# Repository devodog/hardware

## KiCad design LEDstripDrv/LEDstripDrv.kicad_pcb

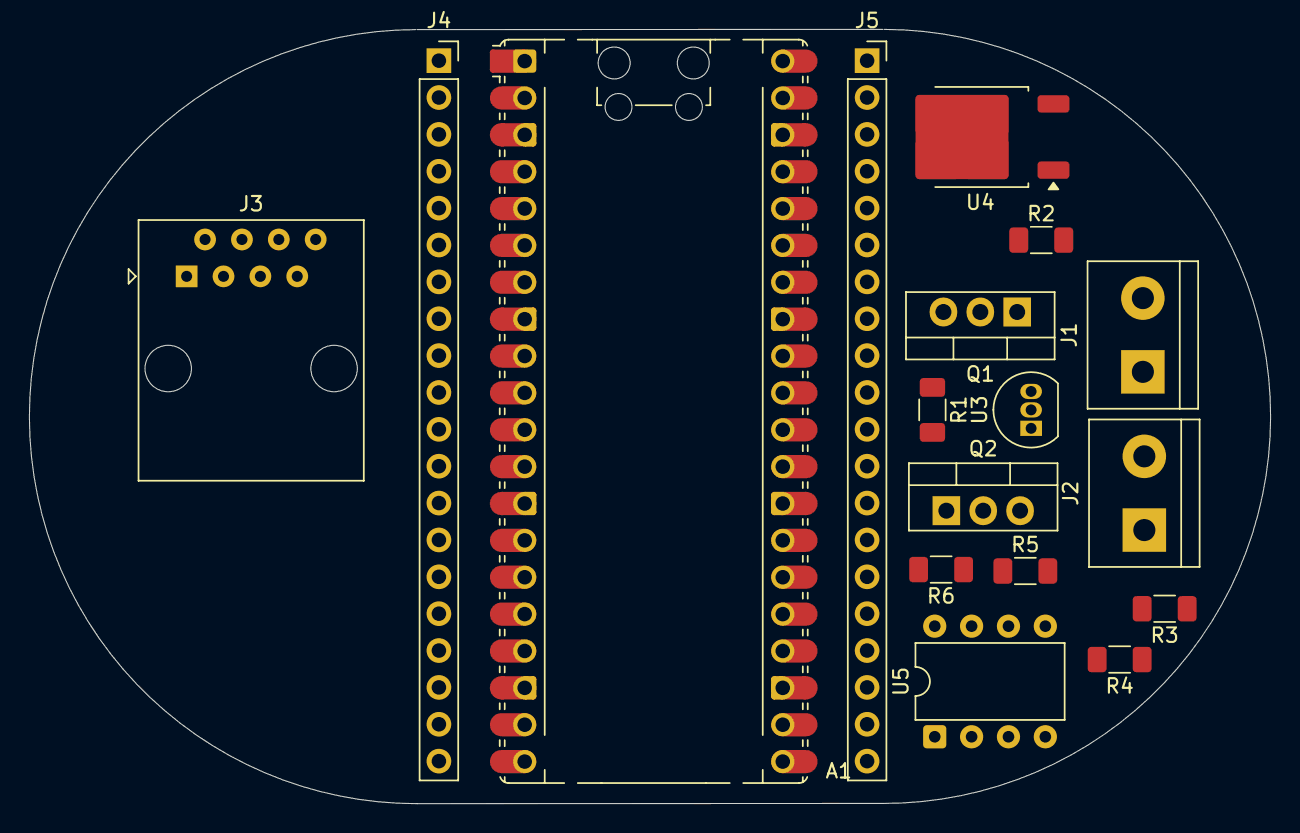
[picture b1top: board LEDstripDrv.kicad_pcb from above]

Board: 2 copper layers, 85.5 x 53.3 mm, 17 parts (0 on the bottom side), 43 nets, no tracks yet.

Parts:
A1: RaspberryPi_Pico; RaspberryPi_Pico_Common_Unspecified
J1, J2: Screw_Terminal_01x02; TerminalBlock_bornier-2_P5.08mm
J3: RJ45; RJ45_Amphenol_54602-x08_Horizontal
J4, J5: Conn_01x20_Pin; PinSocket_1x20_P2.54mm_Vertical
Q1, Q2: IRF540N; TO-220-3_Vertical
R1, R5: 100; R_1206_3216Metric_Pad1.30x1.75mm_HandSolder
R2, R3, R4, R6: 1k; R_1206_3216Metric_Pad1.30x1.75mm_HandSolder
U3: LM35-LP; TO-92_Inline
U4: LF50_TO252; TO-252-2
U5: PC827; DIP-8_W7.62mm

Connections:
+24V: J1.1, J2.1, J3.7, J3.8, U4.1 (VI), U5.6, U5.8
GND: A1.33 (AGND), J3.1, J3.2, Q1.3 (S), Q2.3 (S), R2.1, R3.1, R4.1, R6.1, U3.3 (GND), U4.2 (GND)
unnamed: A1.36 (3V3), J3.6, J5.5
unnamed: A1.37 (3V3_EN), J5.4
unnamed: A1.35 (ADC_VREF), J5.6
unnamed: A1.1 (GPIO0), J4.1
unnamed: A1.2 (GPIO1), J4.2
unnamed: A1.4 (GPIO2), J4.4
unnamed: A1.5 (GPIO3), J4.5
unnamed: A1.6 (GPIO4), J4.6
unnamed: A1.7 (GPIO5), J4.7
unnamed: A1.9 (GPIO6), J4.9
unnamed: A1.10 (GPIO7), J4.10
unnamed: A1.11 (GPIO8), J4.11
unnamed: A1.12 (GPIO9), J4.12
unnamed: A1.14 (GPIO10), J4.14
unnamed: A1.15 (GPIO11), J4.15
unnamed: A1.16 (GPIO12), J4.16
unnamed: A1.17 (GPIO13), J4.17
unnamed: A1.19 (GPIO14), J4.19
unnamed: A1.20 (GPIO15), J4.20
unnamed: A1.21 (GPIO16), J5.20, U5.1
unnamed: A1.22 (GPIO17), J5.19, U5.3
unnamed: A1.24 (GPIO18), J5.17
unnamed: A1.25 (GPIO19), J5.16
unnamed: A1.26 (GPIO20), J5.15
unnamed: A1.27 (GPIO21), J5.14
unnamed: A1.29 (GPIO22), J5.12
unnamed: A1.31 (GPIO26_ADC0), J3.3, J5.10
unnamed: A1.32 (GPIO27_ADC1), J3.4, J5.9
unnamed: A1.34 (GPIO28_ADC2), J5.7, U3.2 (V_{OUT})
unnamed: A1.30 (RUN), J3.5, J5.11
unnamed: A1.40 (VBUS), J5.1
unnamed: A1.39 (VSYS), J5.2, U3.1 (+V_{S}), U4.3 (VO)
unnamed: J1.2, Q1.2 (D)
unnamed: J2.2, Q2.2 (D)
unnamed: A1.3 (GND), A1.8 (GND), A1.13 (GND), A1.18 (GND), A1.23 (GND), A1.28 (GND), A1.38 (GND), J4.3, J4.8, J4.13, J4.18, J5.3, J5.8, J5.13, J5.18
unnamed: Q1.1 (G), R1.2, R2.2
unnamed: Q2.1 (G), R5.2, R6.2
unnamed: R1.1, U5.7
unnamed: R3.2, U5.2
unnamed: R4.2, U5.4
unnamed: R5.1, U5.5

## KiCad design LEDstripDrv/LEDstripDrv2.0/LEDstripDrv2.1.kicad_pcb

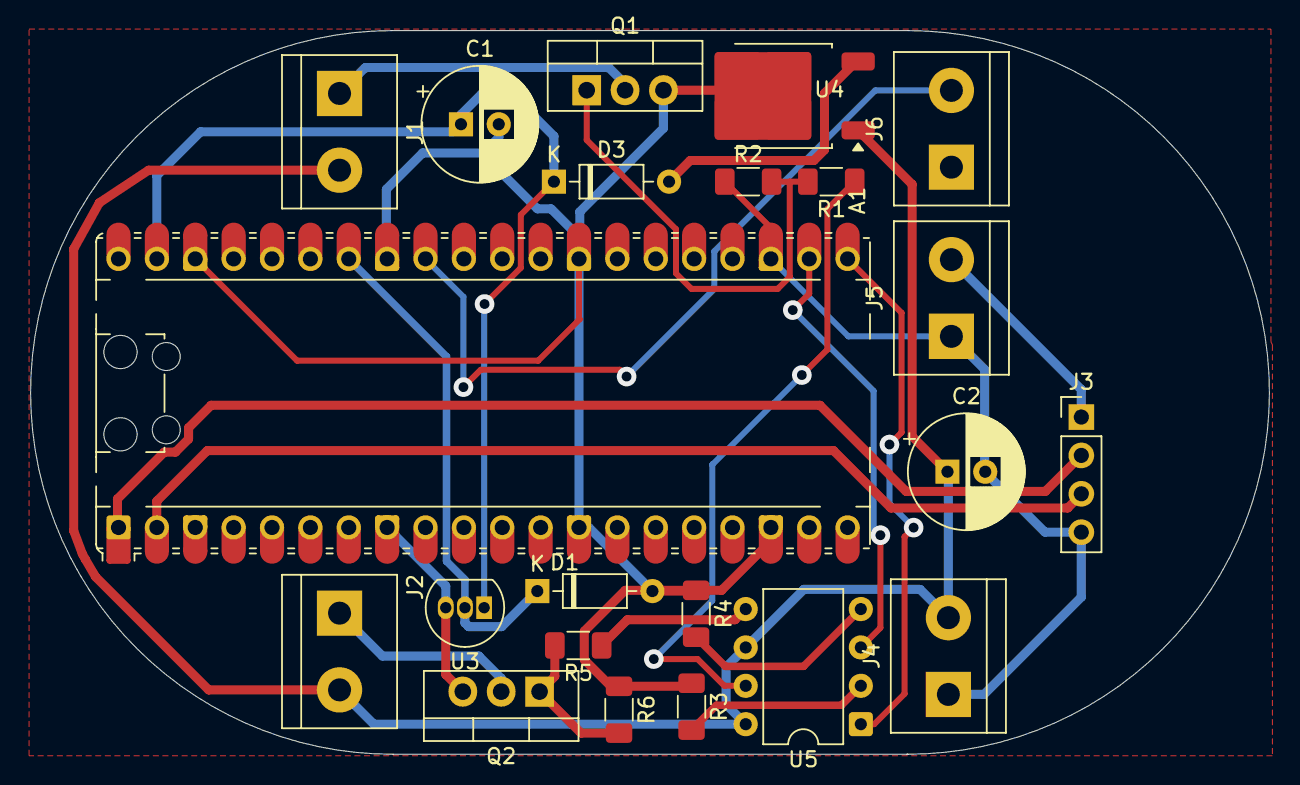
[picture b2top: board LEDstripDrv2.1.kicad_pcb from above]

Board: 2 copper layers, 82.0 x 47.9 mm, 22 parts (0 on the bottom side), 20 nets.

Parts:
A1: RaspberryPi_Pico; RaspberryPi_Pico_Common_Unspecified
C1: 100µF; CP_Radial_D7.5mm_P2.50mm
C2: 100µF30V; CP_Radial_D7.5mm_P2.50mm
D1: 3V; D_DO-35_SOD27_P7.62mm_Horizontal
D3: 1N4149; D_DO-35_SOD27_P7.62mm_Horizontal
J1, J2, J4, J5, J6: Screw_Terminal_01x02; TerminalBlock_bornier-2_P5.08mm
J3: Conn_01x04; PinHeader_1x04_P2.54mm_Vertical
Q1, Q2: IRF540N; TO-220-3_Vertical
R1, R5: 100; R_1206_3216Metric_Pad1.30x1.75mm_HandSolder
R2, R3, R4, R6: 1k; R_1206_3216Metric_Pad1.30x1.75mm_HandSolder
U3: LM35-LP; TO-92_Inline
U4: LF50_TO252; TO-252-2
U5: PC827; DIP-8_W7.62mm

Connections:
+24V: C2.1, J1.2, J2.2, J4.2, U4.1 (VI), U5.6, U5.8
GND: A1.3 (GND), A1.8 (GND), A1.13 (GND), A1.18 (GND), A1.23 (GND), A1.28 (GND), A1.33 (AGND), A1.38 (GND), C1.2, C2.2, D1.2 (A), J3.4, J4.1, J5.1, Q1.3 (S), Q2.3 (S), R2.1, R3.1, R4.1, R6.1, U3.3 (GND), U4.2 (GND)
unnamed: A1.36 (3V3), J3.1, J5.2
unnamed: A1.1 (GPIO0), J3.2
unnamed: A1.2 (GPIO1), J3.3
unnamed: A1.21 (GPIO16), U5.1
unnamed: A1.22 (GPIO17), U5.3
unnamed: A1.31 (GPIO26_ADC0), J6.1
unnamed: A1.32 (GPIO27_ADC1), J6.2
unnamed: A1.34 (GPIO28_ADC2), D1.1 (K), U3.2 (V_{OUT})
unnamed: A1.39 (VSYS), C1.1, D3.1 (K), U3.1 (+V_{S})
unnamed: D3.2 (A), U4.3 (VO)
unnamed: J1.1, Q1.2 (D)
unnamed: J2.1, Q2.2 (D)
unnamed: Q1.1 (G), R1.2, R2.2
unnamed: Q2.1 (G), R5.2, R6.2
unnamed: R1.1, U5.7
unnamed: R3.2, U5.2
unnamed: R4.2, U5.4
unnamed: R5.1, U5.5

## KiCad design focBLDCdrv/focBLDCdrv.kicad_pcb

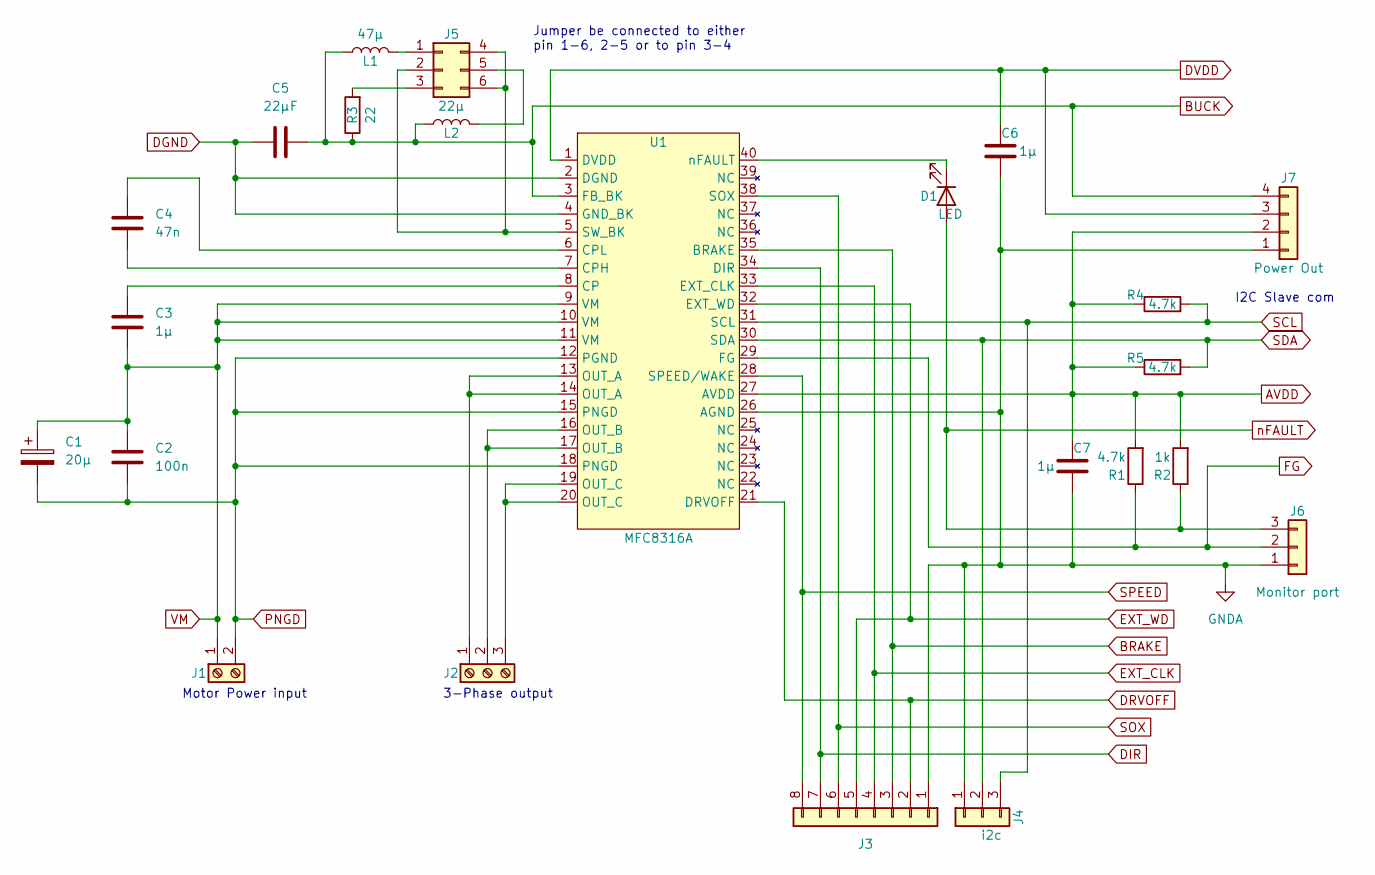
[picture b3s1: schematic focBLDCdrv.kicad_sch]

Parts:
C1: 20µ; CP_Elec_4x3
C2: 100n; C_0805_2012Metric_Pad1.18x1.45mm_HandSolder
C3, C6, C7: 1µ; C_0805_2012Metric_Pad1.18x1.45mm_HandSolder
C4: 47n; C_0805_2012Metric_Pad1.18x1.45mm_HandSolder
C5: 22µF; C_1206_3216Metric_Pad1.33x1.80mm_HandSolder
D1: LED; LED_1206_3216Metric_Pad1.42x1.75mm_HandSolder
J1: Screw_Terminal_01x02; TerminalBlock_bornier-2_P5.08mm
J2: Screw_Terminal_01x03; TerminalBlock_bornier-3_P5.08mm
J3: Conn_01x08; PinHeader_1x08_P2.54mm_Vertical
J4: i2c; PinHeader_1x03_P2.54mm_Vertical
J5: Conn_02x03_Top_Bottom; PinHeader_2x03_P2.54mm_Vertical
J6: Monitor port; PinHeader_1x03_P2.54mm_Vertical
J7: Power Out; PinHeader_1x04_P2.54mm_Vertical
L1: 47µ; L_1206_3216Metric
L2: 22µ; L_1206_3216Metric
R1, R4, R5: 4.7k; R_0805_2012Metric_Pad1.20x1.40mm_HandSolder
R2: 1k; R_0805_2012Metric_Pad1.20x1.40mm_HandSolder
R3: 22; R_1206_3216Metric_Pad1.30x1.75mm_HandSolder
U1: MFC8316A; Texas_VQFN-N40_EP7.00x5.00mm_ThermalVias

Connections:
AVDD: C7.1, J7.2, R1.2, R2.2, R4.1, R5.1, U1.27 (AVDD)
BRAKE: J3.3, U1.35 (BRAKE)
BUCK: C5.2, J7.4, L1.1, L2.1, R3.1, U1.3 (FB_BK)
DGND: C5.1, U1.2 (DGND), U1.4 (GND_BK)
DIR: J3.7, U1.34 (DIR)
DRVOFF: J3.2, U1.21 (DRVOFF)
DVDD: C6.1, J7.3, U1.1 (DVDD)
EXT_CLK: J3.4, U1.33 (EXT_CLK)
EXT_WD: J3.5, U1.32 (EXT_WD)
FG: J6.2, R1.1, U1.29 (FG)
GNDA: C6.2, C7.2, J3.1, J4.1, J6.1, J7.1, U1.26 (AGND), U1.41
unnamed: C3.1, U1.8 (CP)
unnamed: C4.1, U1.7 (CPH)
unnamed: C4.2, U1.6 (CPL)
unnamed: D1.1 (K), U1.40 (nFAULT)
unnamed: J2.1, U1.13 (OUT_A), U1.14 (OUT_A)
unnamed: J2.2, U1.16 (OUT_B), U1.17 (OUT_B)
unnamed: J2.3, U1.19 (OUT_C), U1.20 (OUT_C)
unnamed: J5.1, L1.2
unnamed: J5.2, J5.4, J5.6, U1.5 (SW_BK)
unnamed: J5.3, R3.2
unnamed: J5.5, L2.2
PNGD: C1.2, C2.2, J1.2, U1.12 (PGND), U1.15 (PNGD), U1.18 (PNGD)
SCL: J4.3, R4.2, U1.31 (SCL)
SDA: J4.2, R5.2, U1.30 (SDA)
SOX: J3.6, U1.38 (SOX)
SPEED: J3.8, U1.28 (SPEED/WAKE)
VM: C1.1, C2.1, C3.2, J1.1, U1.9 (VM), U1.10 (VM), U1.11 (VM)
nFAULT: D1.2 (A), J6.3, R2.1

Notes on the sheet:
3-Phase output
Jumper be connected to either pin 1-6, 2-5 or to pin 3-4
Motor Power input
I2C Slave com

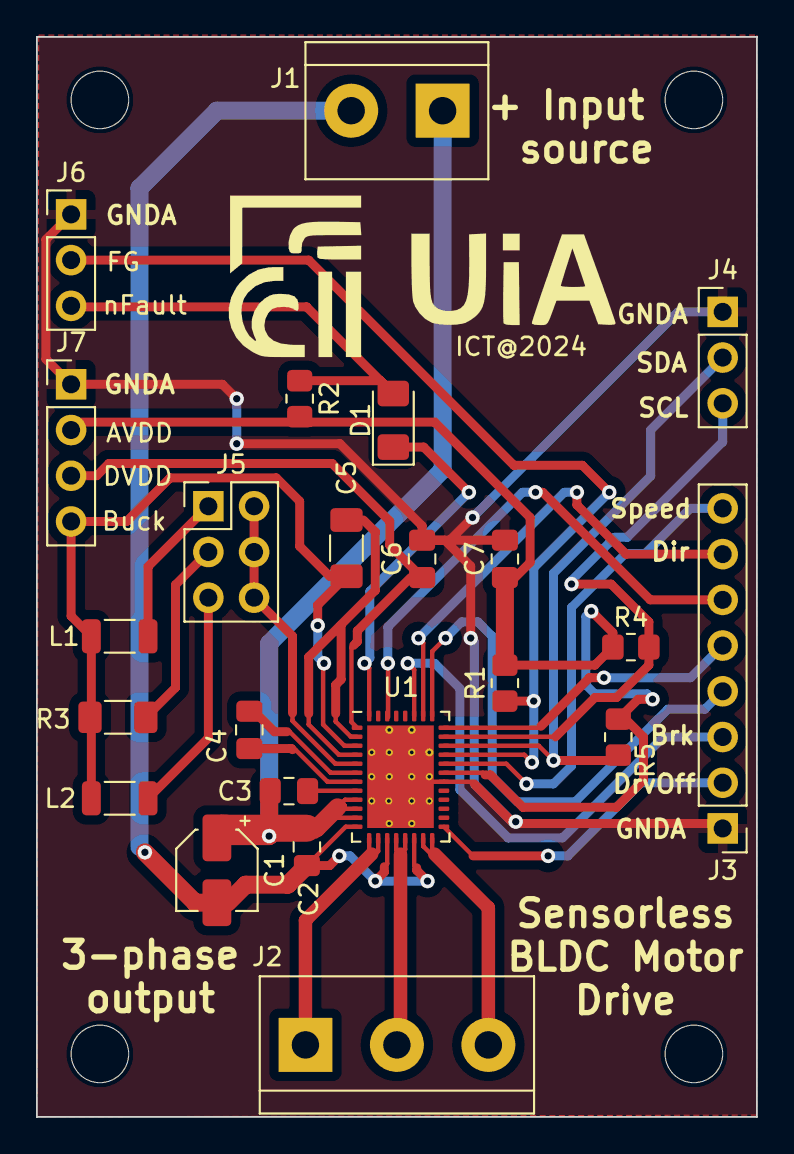
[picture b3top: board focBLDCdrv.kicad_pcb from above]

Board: 2 copper layers, 40.0 x 60.0 mm, 23 parts (0 on the bottom side), 29 nets.

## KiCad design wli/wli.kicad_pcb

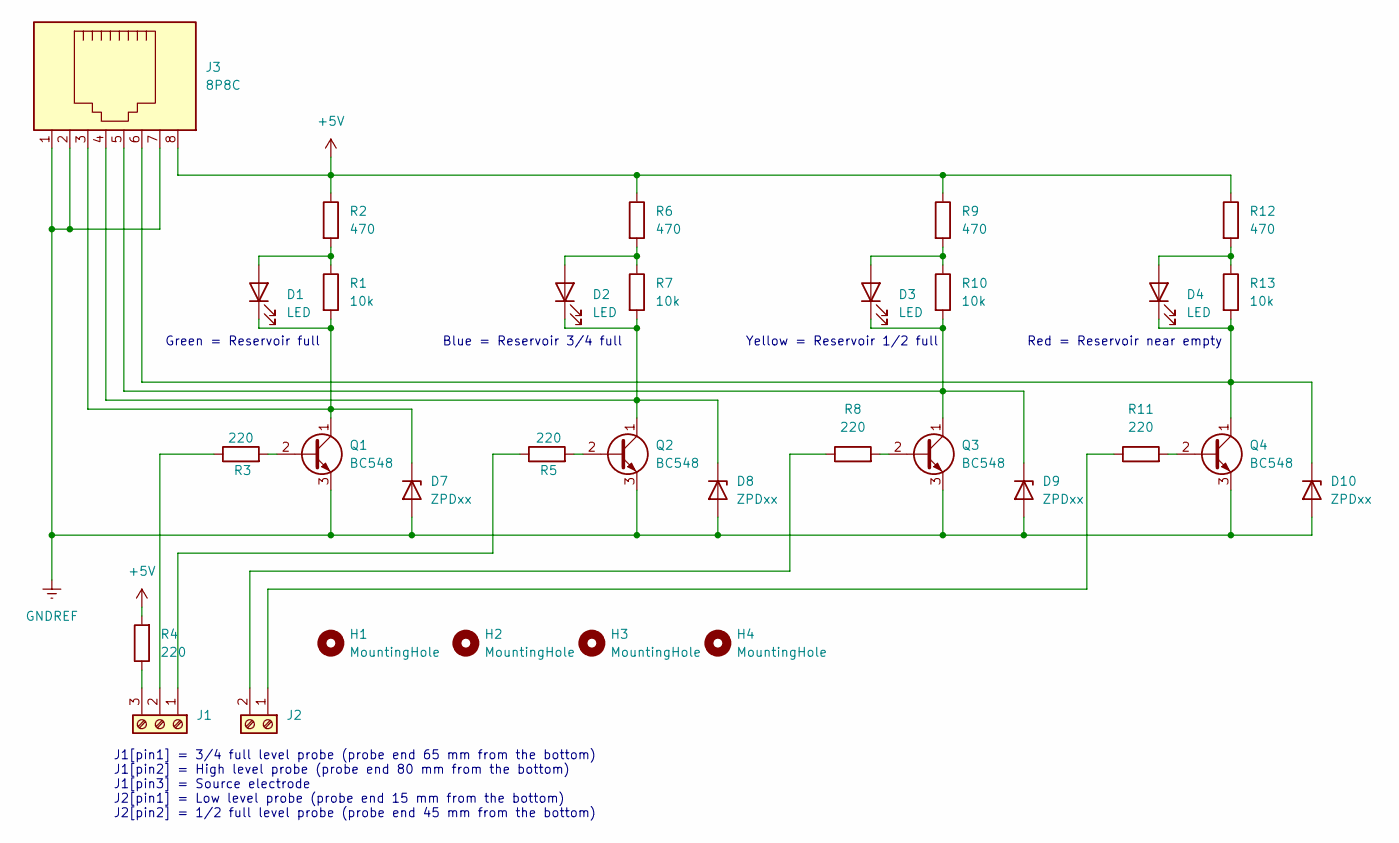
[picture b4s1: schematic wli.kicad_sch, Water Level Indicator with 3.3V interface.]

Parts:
D1, D2, D3, D4: LED; LED_D5.0mm
D7, D8, D9, D10: ZPDxx; D_DO-35_SOD27_P10.16mm_Horizontal
H1, H2, H3, H4: MountingHole; MountingHole_3.2mm_M3
J1: Screw_Terminal_01x03; TerminalBlock_Phoenix_MKDS-1,5-3_1x03_P5.00mm_Horizontal
J2: Screw_Terminal_01x02; TerminalBlock_Phoenix_MKDS-1,5-2-5.08_1x02_P5.08mm_Horizont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
J3: 8P8C; RJ45_Amphenol_54602-x08_Horizontal
Q1, Q2, Q3, Q4: BC548; TO-92L_HandSolder
R1, R7, R10, R13: 10k; R_Axial_DIN0207_L6.3mm_D2.5mm_P10.16mm_Horizontal
R2, R6, R9, R12: 470; R_Axial_DIN0207_L6.3mm_D2.5mm_P10.16mm_Horizontal
R3, R4, R5, R8, R11: 220; R_Axial_DIN0207_L6.3mm_D2.5mm_P10.16mm_Horizontal

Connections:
+5V: J3.8, R2.1, R4.2, R6.1, R9.1, R12.1
GNDREF: D7.2 (A), D8.2 (A), D9.2 (A), D10.2 (A), J3.1, J3.2, J3.7, Q1.3 (E), Q2.3 (E), Q3.3 (E), Q4.3 (E)
unnamed: D1.2 (A), R1.1, R2.2
unnamed: D1.1 (K), D7.1 (K), J3.3, Q1.1 (C), R1.2
unnamed: D2.2 (A), R6.2, R7.1
unnamed: D2.1 (K), D8.1 (K), J3.4, Q2.1 (C), R7.2
unnamed: D3.2 (A), R9.2, R10.1
unnamed: D3.1 (K), D9.1 (K), J3.5, Q3.1 (C), R10.2
unnamed: D4.2 (A), R12.2, R13.1
unnamed: D4.1 (K), D10.1 (K), J3.6, Q4.1 (C), R13.2
unnamed: J1.1, R5.1
unnamed: J1.2, R3.1
unnamed: J1.3, R4.1
unnamed: J2.1, R11.1
unnamed: J2.2, R8.1
unnamed: Q1.2 (B), R3.2
unnamed: Q2.2 (B), R5.2
unnamed: Q3.2 (B), R8.2
unnamed: Q4.2 (B), R11.2

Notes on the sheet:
Blue = Reservoir 3/4 full
Green = Reservoir full
Yellow = Reservoir 1/2 full
J1[pin1] = 3/4 full level probe (probe end 65 mm from the bottom) J1[pin2] = High level probe (probe end 80 mm from the bottom) J1[pin3] = Source electrode J2[pin1] = Low level probe (probe end 15 mm from the bottom) J2[pin2] = 1/2 full level probe (probe end 45 mm from the bottom)
Red = Reservoir near empty

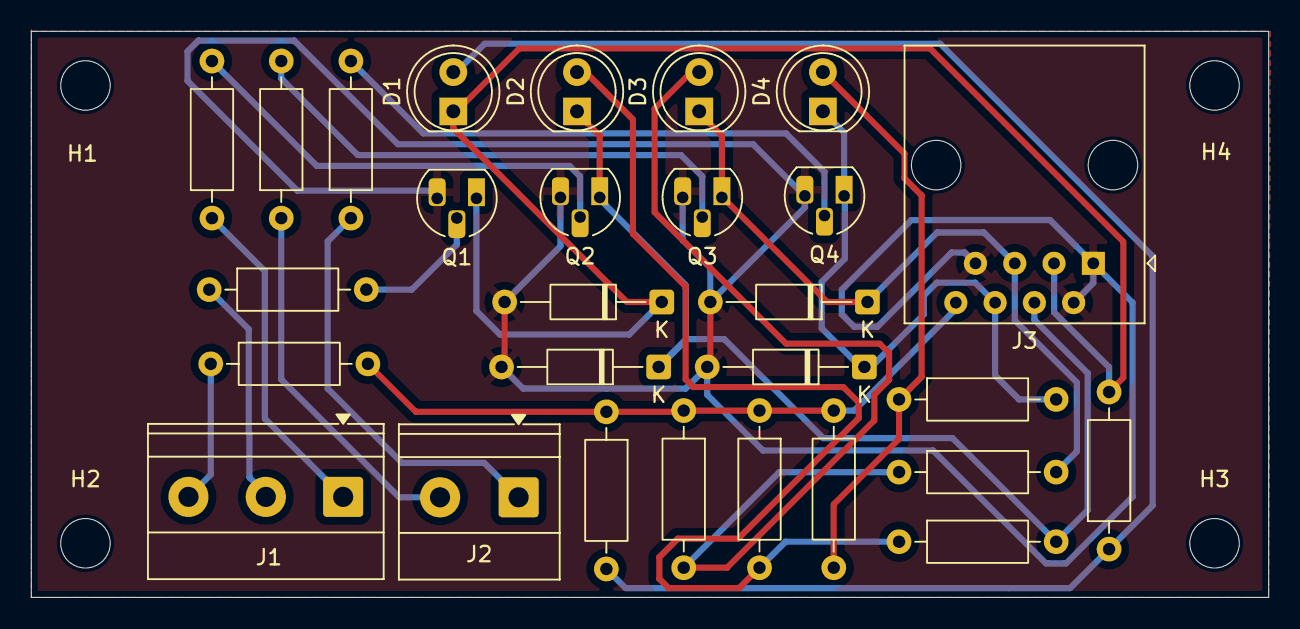
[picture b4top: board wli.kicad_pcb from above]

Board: 2 copper layers, 80.0 x 36.6 mm, 32 parts (0 on the bottom side), 19 nets.
